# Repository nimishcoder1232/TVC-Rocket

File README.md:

# TVC-Rocket
This is the repo for my TVC rocket that took two years to develop. 

This is the last revision that actually worked. At the end of my 8th-grade year, there were many other iterations, but I have lost the documentation for those. 

Thumbnail/screenshot: 

PCB: 

The goal of this was to make a thrust vector controlled rocket that can stabilize itself on the way up. This goal ended up being completely successful. 
Demo: 
https://drive.google.com/file/d/10EWHrPkHGs0dUHyr1Sujefc27muy-WCw/view?usp=sharing

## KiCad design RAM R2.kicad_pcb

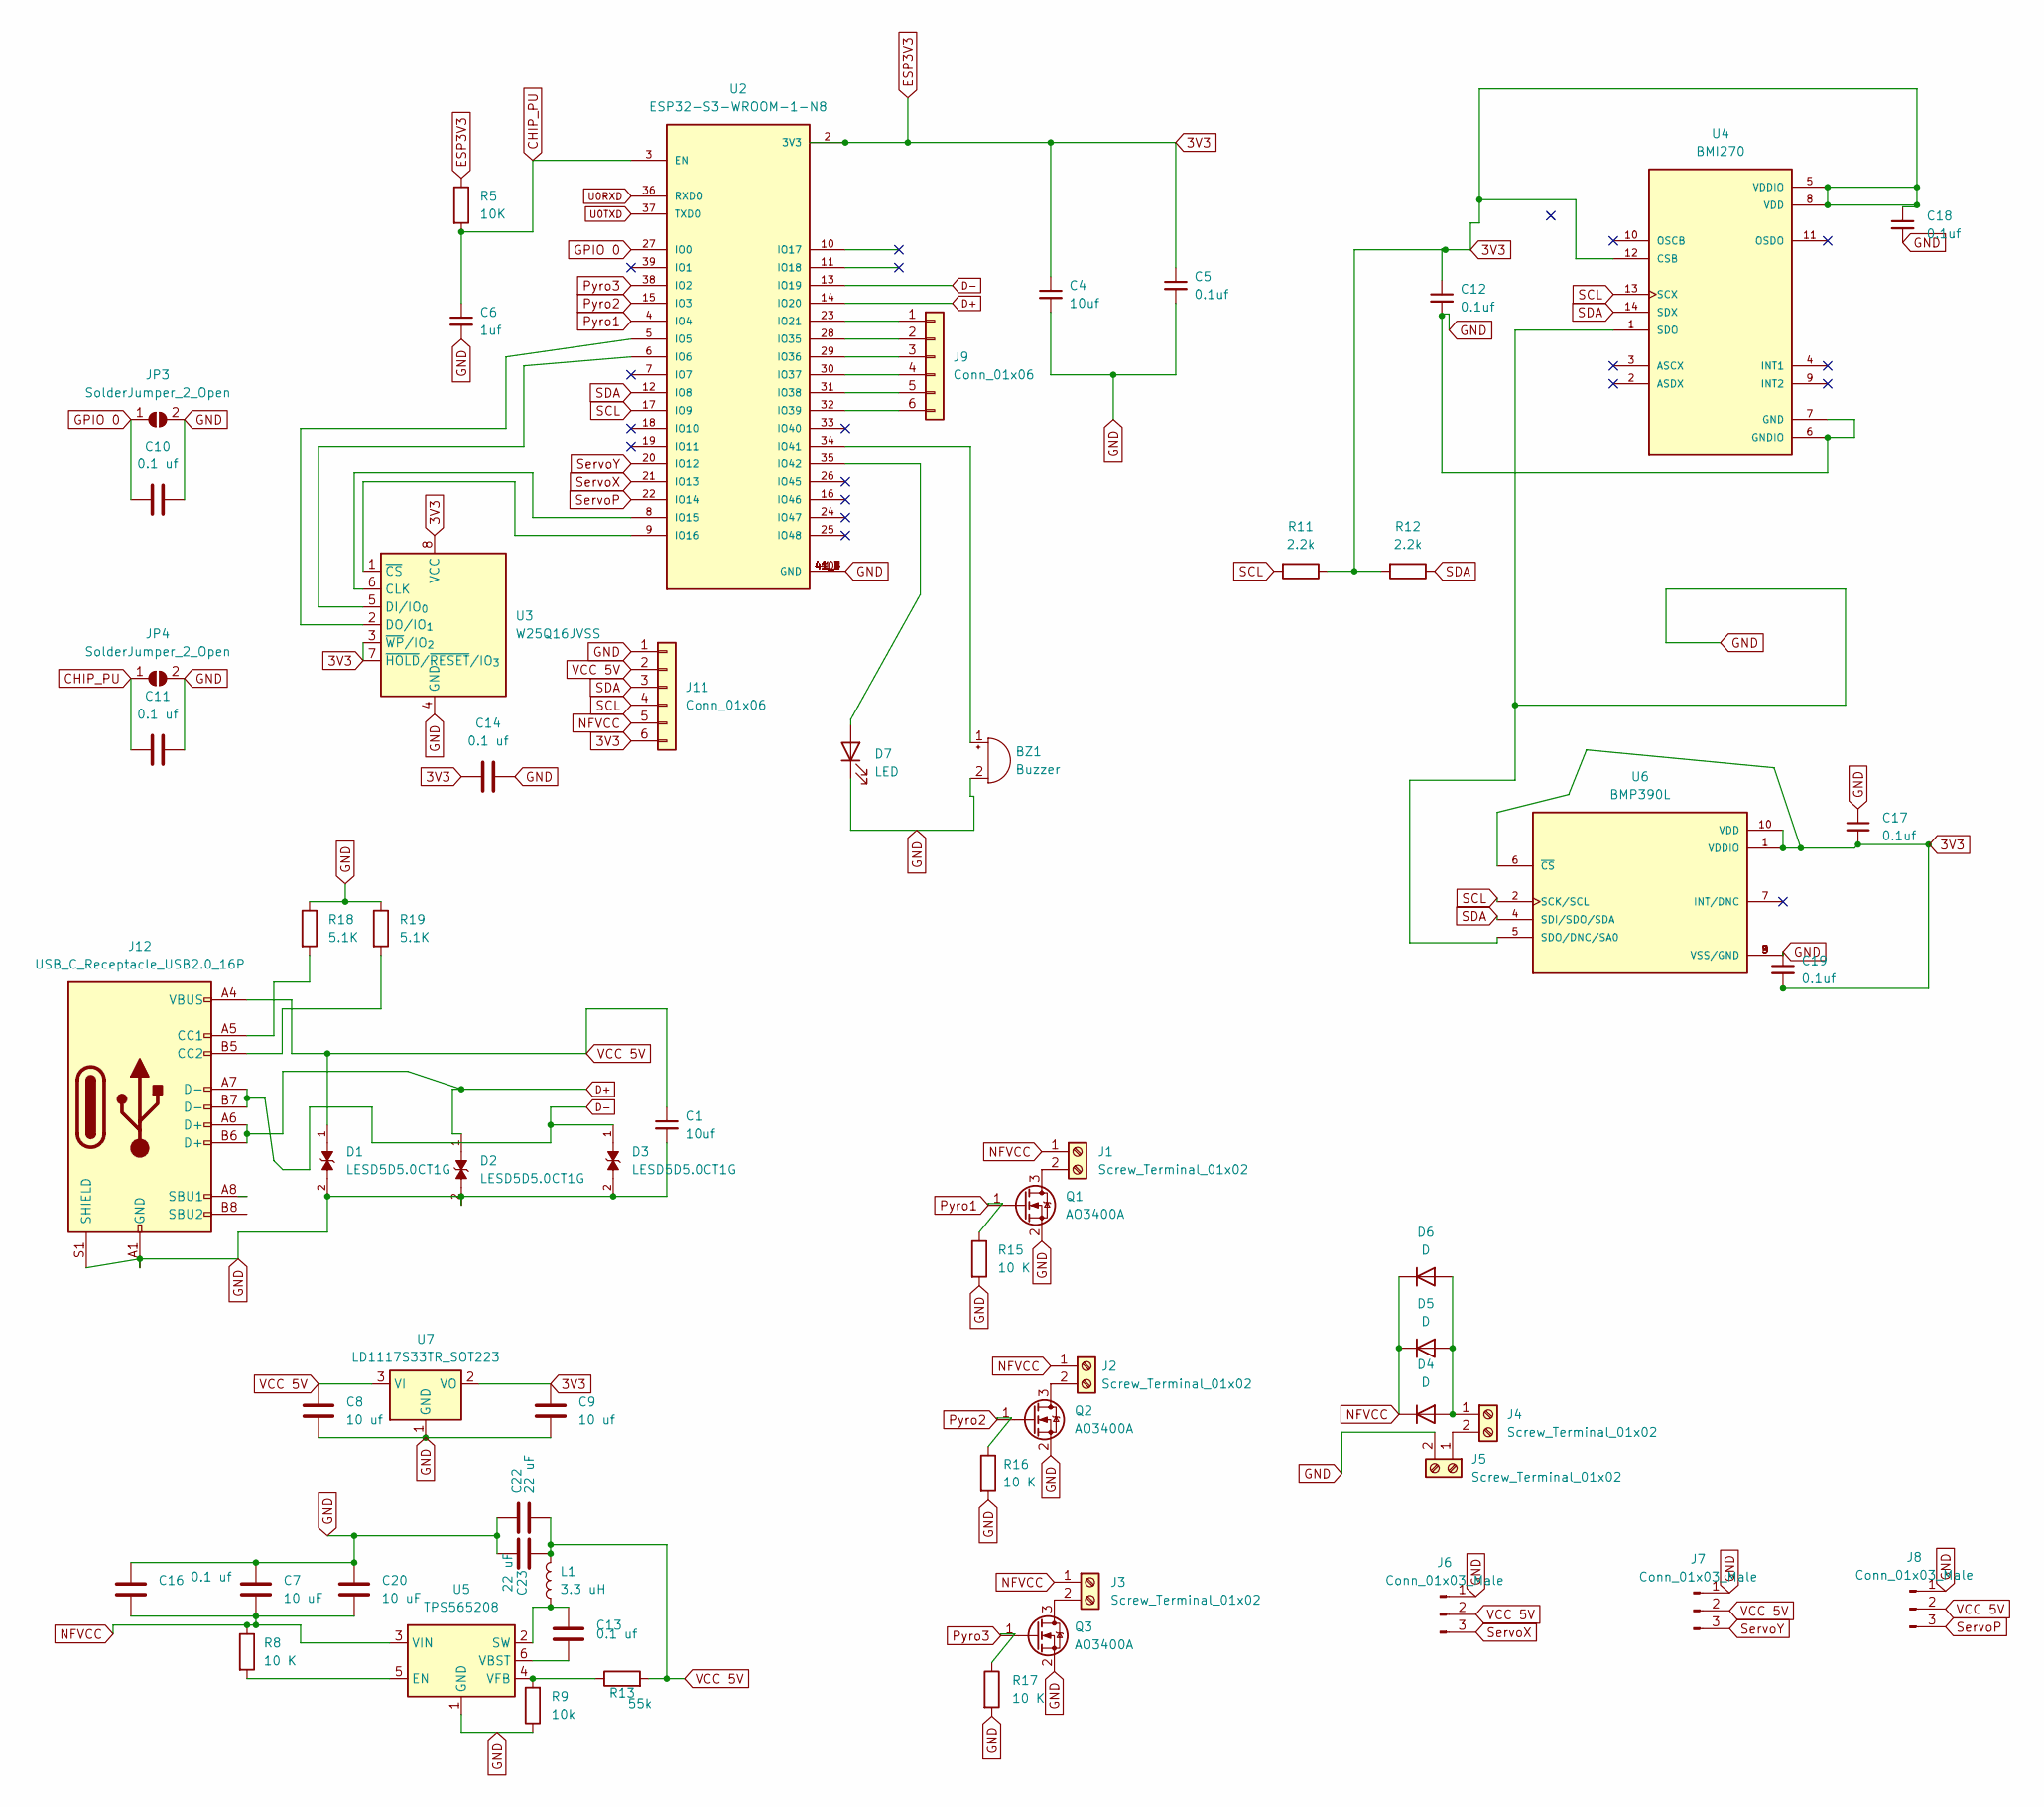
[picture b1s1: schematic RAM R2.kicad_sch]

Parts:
BZ1: Buzzer; Buzzer_TDK_PS1240P02BT_D12.2mm_H6.5mm
C1, C4: 10uf; C_0805_2012Metric
C5, C12, C17, C18, C19: 0.1uf; C_0805_2012Metric
C6: 1uf; C_0805_2012Metric
C7, C20: 10 uF; C_0805_2012Metric
C8, C9: 10 uf; C_0805_2012Metric
C10, C11, C13, C14, C16: 0.1 uf; C_0805_2012Metric
C22, C23: 22 uF; C_0805_2012Metric
D1, D2, D3: LESD5D5.0CT1G; TVS_LESD5D5.0CT1G; PARTREV O
D4, D5, D6: D; D_SMA
D7: LED; LED_0805_2012Metric
J1, J2, J3, J4, J5: Screw_Terminal_01x02; TerminalBlock_4Ucon_1x02_P3.50mm_Horizontal
J6, J7, J8: Conn_01x03_Male; PinHeader_1x03_P2.54mm_Vertical
J9, J11: Conn_01x06; 6pad genaric
J12: USB_C_Receptacle_USB2.0_16P; USB_C_Receptacle_GCT_USB4105-xx-A_16P_TopMnt_Horizontal
JP3, JP4: SolderJumper_2_Open; SW_PUSH_6mm_H5mm
L1: 3.3 uH; L_0805_2012Metric
Q1, Q2, Q3: AO3400A; SOT-23
R5: 10K; R_0805_2012Metric
R8, R15, R16, R17: 10 K; R_0805_2012Metric
R9: 10k; R_0805_2012Metric
R11, R12: 2.2k; R_0805_2012Metric
R13: 55k; R_0805_2012Metric
R18, R19: 5.1K; R_0805_2012Metric
U2: ESP32-S3-WROOM-1-N8; XCVR_ESP32-S3-WROOM-1-N8
U3: W25Q16JVSS; SOIC-8_5.3x5.3mm_P1.27mm
U4: BMI270; XDCR_BMI270
U5: TPS565208; SOT-23-6
U6: BMP390L; XDCR_BMP390L; PARTREV 1.7
U7: LD1117S33TR_SOT223; SOT-223-3_TabPin2

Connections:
3V3: C4.1, C5.1, C9.1, C12.1, C14.2, C17.2, C18.1, C19.2, J11.6, R5.1, R11.1, R12.2, U2.2 (3V3), U3.3 (~WP/IO_{2}), U3.7 (~HOLD/~RESET/IO_{3}), U3.8 (VCC), U4.5 (VDDIO), U4.8 (VDD), U4.12 (CSB), U6.1 (VDDIO), U6.6 (~CS), U6.10 (VDD), U7.2 (VO)
CHIP_PU: C6.1, C11.2, JP4.1 (A), R5.2, U2.3 (EN)
D+: D2.1, J12.A6 (D+), J12.B6 (D+), U2.14 (IO20)
D-: D3.1, J12.A7 (D-), J12.B7 (D-), U2.13 (IO19)
GND: BZ1.2 (+), C1.2, C4.2, C5.2, C6.2, C7.1, C8.2, C9.2, C10.1, C11.1, C12.2, C14.1, C16.1, C17.1, C18.2, C19.1, C20.1, C22.1, C23.1, D1.2, D2.2, D3.2, D7.1 (K), J5.2, J6.1, J7.1, J8.1, J11.1, J12.A1 (GND), J12.A12 (GND), J12.B1 (GND), J12.B12 (GND), J12.S1 (SHIELD), JP3.2 (B), JP4.2 (B), Q1.2 (S), Q2.2 (S), Q3.2 (S), R9.1, R15.2, R16.2, R17.2, R18.1, R19.1, U2.1 (GND), U2.40 (GND), U2.41_1 (GND), U2.41_2 (GND), U2.41_3 (GND), U2.41_4 (GND), U2.41_5 (GND), U2.41_6 (GND), U2.41_7 (GND), U2.41_8 (GND), U2.41_9 (GND), U3.4 (GND), U4.1 (SDO), U4.6 (GNDIO), U4.7 (GND), U5.1 (GND), U6.3 (VSS/GND), U6.5 (SDO/DNC/SA0), U6.8 (VSS/GND), U6.9 (VSS/GND), U7.1 (GND)
GPIO 0: C10.2, JP3.1 (A), U2.27 (IO0)
NFVCC: C7.2, C16.2, C20.2, D4.1 (K), D5.1 (K), D6.1 (K), J1.1, J2.1, J3.1, J11.5, R8.1, U5.3 (VIN)
unnamed: BZ1.1 (-), U2.34 (IO41)
unnamed: D4.2 (A), D5.2 (A), D6.2 (A), J4.1
unnamed: D7.2 (A), U2.35 (IO42)
unnamed: J1.2, Q1.3 (D)
unnamed: J2.2, Q2.3 (D)
unnamed: J3.2, Q3.3 (D)
unnamed: J4.2, J5.1
unnamed: J9.1, U2.23 (IO21)
unnamed: J9.2, U2.28 (IO35)
unnamed: J9.3, U2.29 (IO36)
unnamed: J9.4, U2.30 (IO37)
unnamed: J9.5, U2.31 (IO38)
unnamed: J9.6, U2.32 (IO39)
unnamed: J12.A5 (CC1), R18.2
unnamed: J12.B5 (CC2), R19.2
unnamed: U2.5 (IO5), U3.2 (DO/IO_{1})
unnamed: U2.6 (IO6), U3.5 (DI/IO_{0})
unnamed: U2.8 (IO15), U3.6 (CLK)
unnamed: U2.9 (IO16), U3.1 (~CS)
unnamed: R8.2, U5.5 (EN)
unnamed: C13.1, L1.1, U5.2 (SW)
unnamed: C13.2, U5.6 (VBST)
unnamed: R9.2, R13.1, U5.4 (VFB)
Pyro1: Q1.1 (G), R15.1, U2.4 (IO4)
Pyro2: Q2.1 (G), R16.1, U2.15 (IO3)
Pyro3: Q3.1 (G), R17.1, U2.38 (IO2)
SCL: J11.4, R11.2, U2.17 (IO9), U4.13 (SCX), U6.2 (SCK/SCL)
SDA: J11.3, R12.1, U2.12 (IO8), U4.14 (SDX), U6.4 (SDI/SDO/SDA)
ServoP: J8.3, U2.22 (IO14)
ServoX: J6.3, U2.21 (IO13)
ServoY: J7.3, U2.20 (IO12)
U0RXD: U2.36 (RXD0)
U0TXD: U2.37 (TXD0)
VCC 5V: C1.1, C8.1, C22.2, C23.2, D1.1, J6.2, J7.2, J8.2, J11.2, J12.A4 (VBUS), J12.A9 (VBUS), J12.B4 (VBUS), J12.B9 (VBUS), L1.2, R13.2, U7.3 (VI)

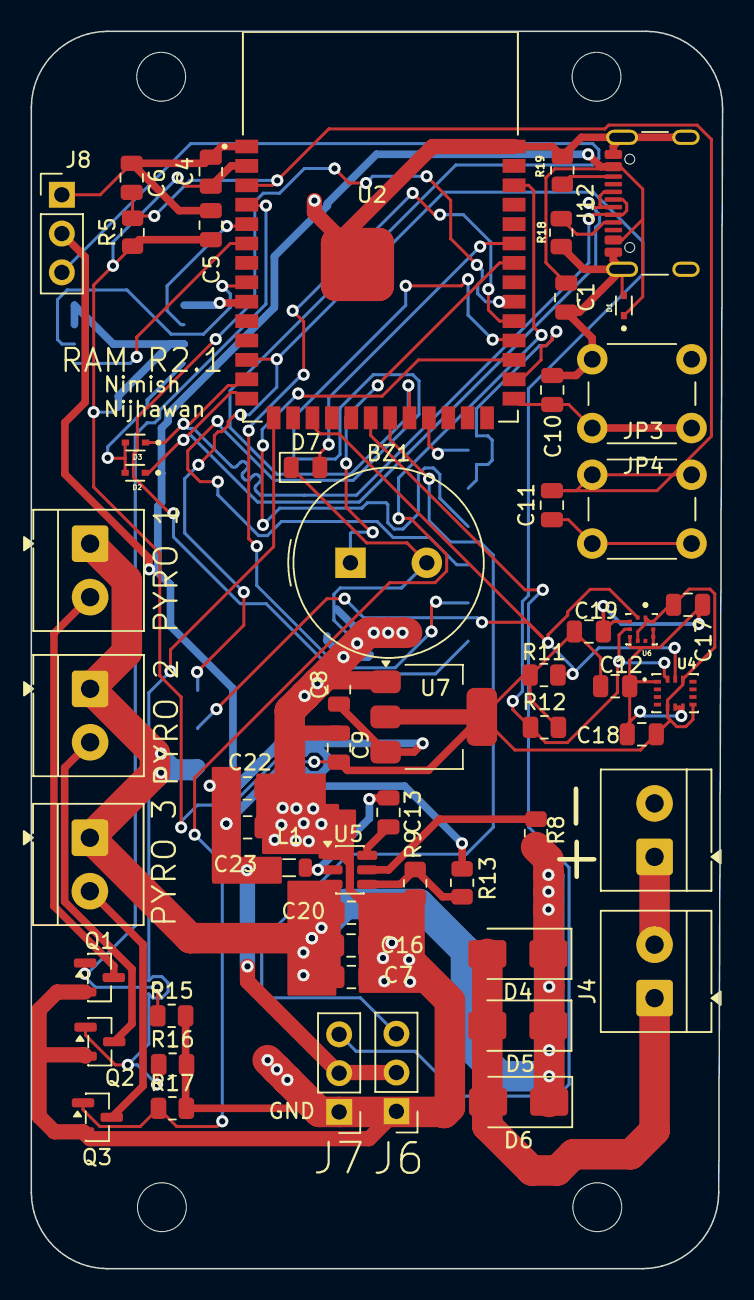
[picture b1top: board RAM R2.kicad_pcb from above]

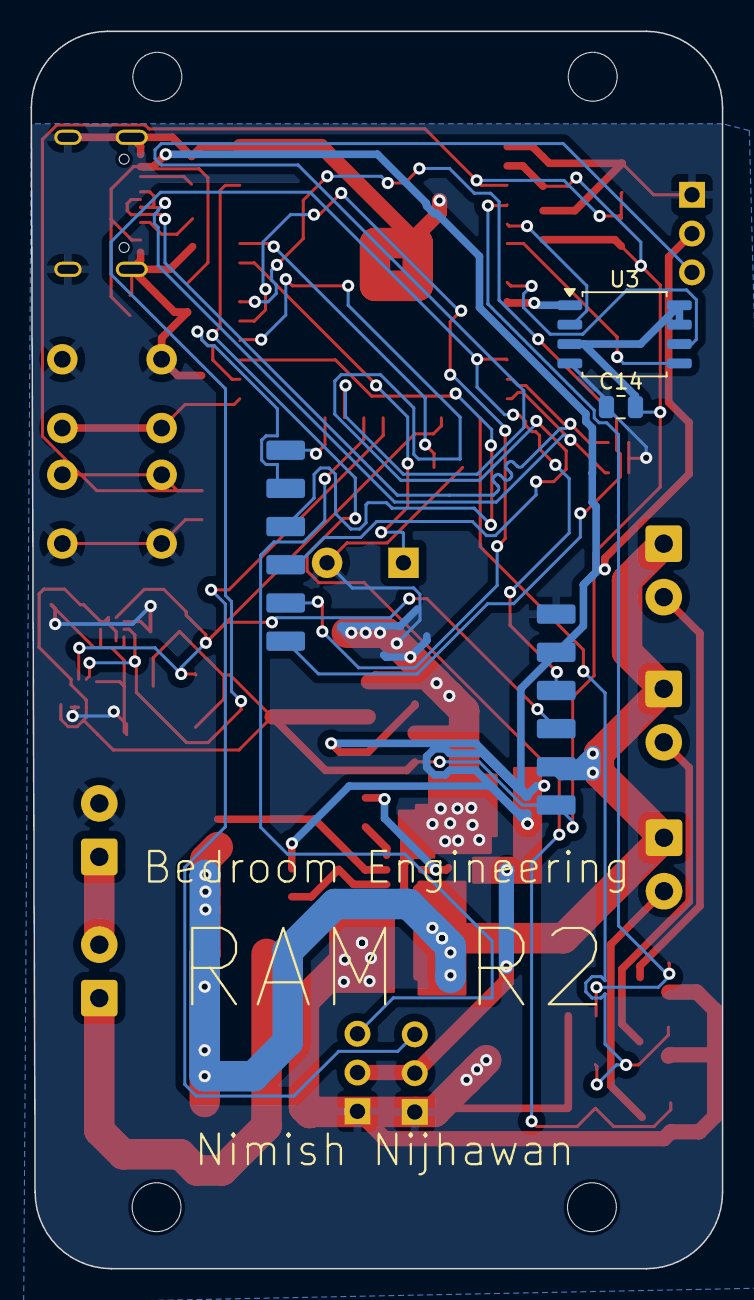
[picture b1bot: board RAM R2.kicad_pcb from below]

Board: 2 copper layers, 45.2 x 81.0 mm, 61 parts (4 on the bottom side), 39 nets.

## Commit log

2026-06-16 Rename Final ROcket.step.zip to CAD/Final ROcket.step.zip
2026-06-16 Rename RAM R2.kicad_sch to PCB/RAM R2.kicad_sch
2026-06-16 Rename RAM R2.kicad_pcb to PCB/RAM R2.kicad_pcb
2026-06-16 Rename RAM R2.kicad_pro to PCB/RAM R2.kicad_pro
2026-06-16 Rename RAM R2.kicad_prl to PCB/RAM R2.kicad_prl
2026-06-16 Expand README with project details and images
    Added additional details about the rocket's development and included images of the PCB.
2026-06-18 Rename Drone BOMB - Sheet1.csv to BOM.csv
